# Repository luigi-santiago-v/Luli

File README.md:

# Luli Hydroponics

## Project Overview
This project aims to create a user-friendly, data-driven, and internet-connected hydroponics system. Targeting food deserts, it offers a solution for accessible nutritious food through a smart home appliance. The system integrates temperature/humidity, light intensity, and water pH sensors, along with UV lighting, a water reservoir, a pump, and a microcontroller into a single appliance. It provides real-time plant health and nutrient data, enhanced by a community-driven web application for sharing insights and tips.

## Key Features

- Comprehensive sensor suite for real-time monitoring
- UV lighting and water management for optimal plant growth
- Community web application for knowledge and tips exchange
  - Python Flask + MongoDB backend
- Designed with food deserts and local community reliance in mind
- **Budget:** $500
- **Duration:** 9 months

## Goals
Develop an open-source hydroponic system to enable community-driven, urban agriculture, addressing the challenge of food deserts and their impact on academic performance. The project focuses on simplifying the hydroponics process for beginners, providing a robust system for easy monitoring and maintenance, and fostering community engagement to sustain interest and success in hydroponic gardening.

## Milestones
- Research, design, and component sourcing
- System assembly and testing
- Creation of a functioning prototype from OSB featuring integrated control and monitoring systems
- Demonstration of prototype efficacy with basic crop growth

## Problem Addressed
Tackles the challenges faced by urban growers, including knowledge barriers and the need for continuous system maintenance. Aims to motivate and support users from construction through to the ongoing cultivation process, making hydroponic gardening accessible and engaging.

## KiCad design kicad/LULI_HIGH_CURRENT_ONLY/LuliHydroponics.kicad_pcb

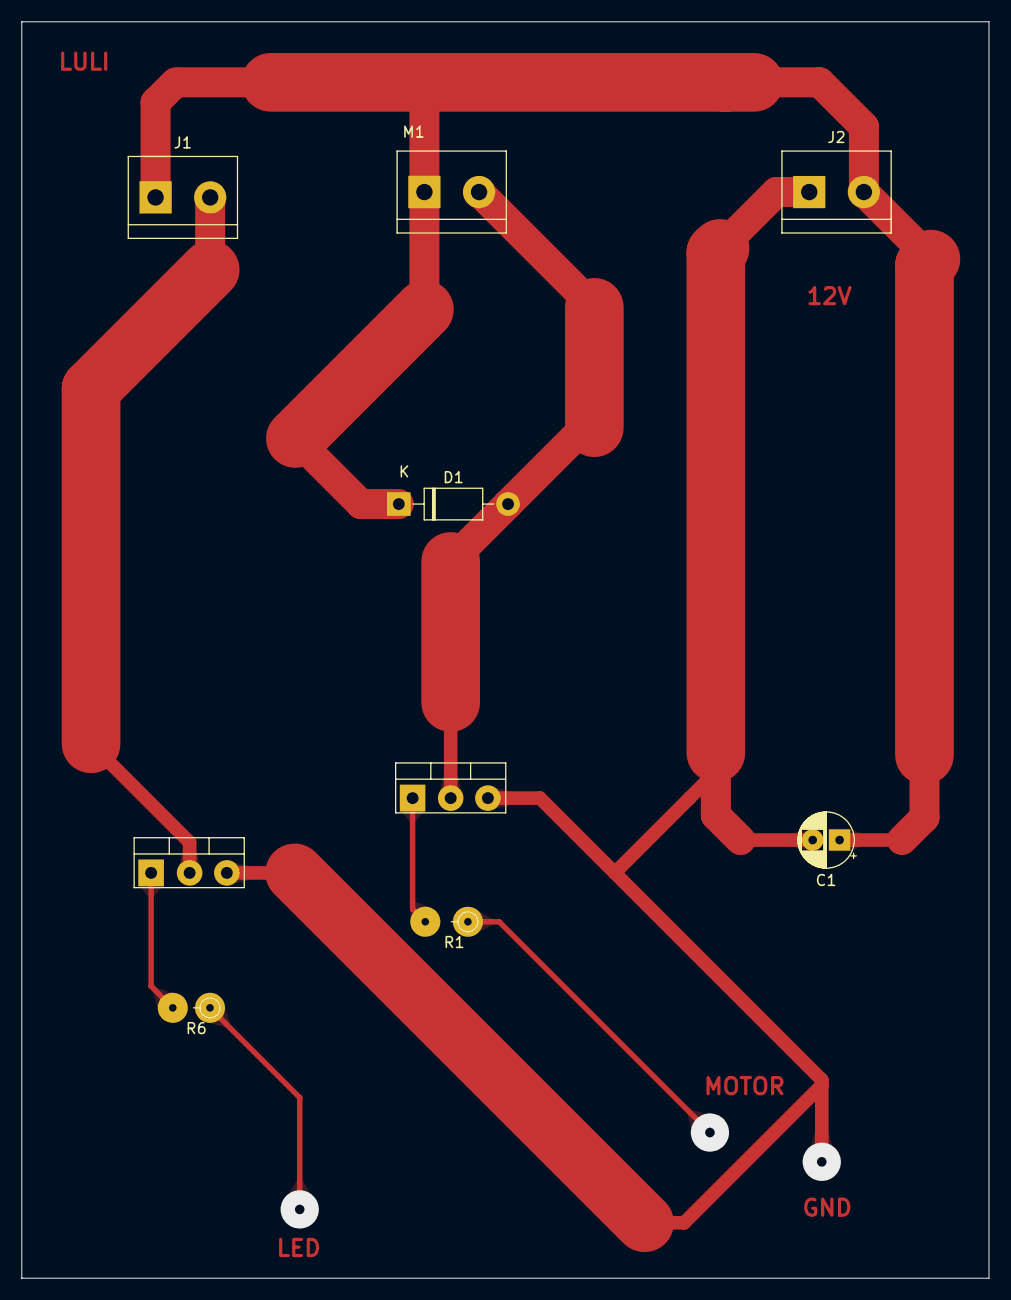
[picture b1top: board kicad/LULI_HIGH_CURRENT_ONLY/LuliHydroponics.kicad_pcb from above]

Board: 2 copper layers, 89.9 x 116.9 mm, 9 parts (0 on the bottom side), 6 nets.

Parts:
C1: 220µF; CP_Radial_D5.0mm_P2.50mm
D1: 1N4001; D_DO-41_SOD81_P10.16mm_Horizontal
J1, J2: Screw_Terminal_01x02; TerminalBlock_bornier-2_P5.08mm
M1: Motor_DC; TerminalBlock_bornier-2_P5.08mm
Q1, Q2: IRLZ34N; TO-220-3_Vertical
R1, R6: 1.0kΩ; R_Axial_DIN0204_L3.6mm_D1.6mm_P2.54mm_Vertical

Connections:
GND: C1.2, J2.1, Q1.3 (S), Q2.3 (S)
unnamed: D1.2 (A), M1.2 (-), Q1.2 (D)
unnamed: J1.2, Q2.2 (D)
unnamed: Q1.1 (G), R1.2
unnamed: Q2.1 (G), R6.2
VCC: C1.1, D1.1 (K), J1.1, J2.2, M1.1 (+)

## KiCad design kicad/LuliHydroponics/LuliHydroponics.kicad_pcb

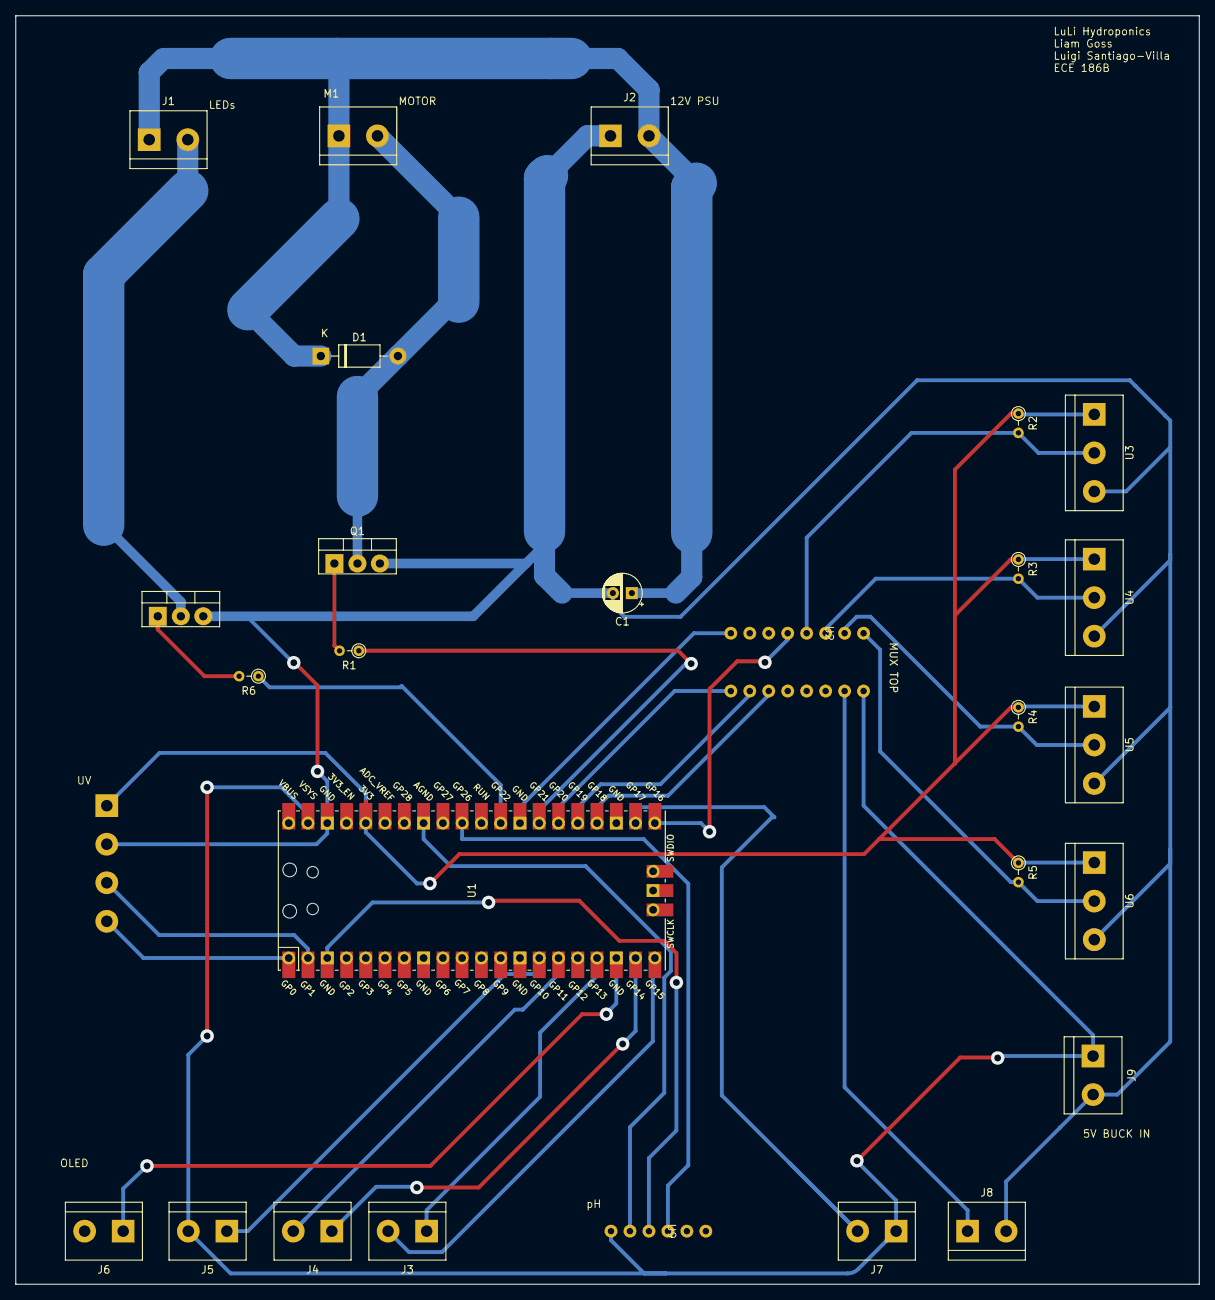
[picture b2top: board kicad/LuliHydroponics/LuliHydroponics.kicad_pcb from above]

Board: 2 copper layers, 156.0 x 167.2 mm, 28 parts (1 on the bottom side), 32 nets.

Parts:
C1: 220µF; CP_Radial_D5.0mm_P2.50mm
D1: 1N4001; D_DO-41_SOD81_P10.16mm_Horizontal
J1, J2, J3, J4, J5, J6, J7, J8, J9: Screw_Terminal_01x02; TerminalBlock_bornier-2_P5.08mm
J10: Screw_Terminal_01x05; TerminalBlock_bornier-4_P5.08mm
M1: Motor_DC; TerminalBlock_bornier-2_P5.08mm
Q1, Q2: IRLZ34N; TO-220-3_Vertical
R1, R6: 1.0kΩ; R_Axial_DIN0204_L3.6mm_D1.6mm_P2.54mm_Vertical
R2, R3, R4, R5: 4.7kΩ; R_Axial_DIN0204_L3.6mm_D1.6mm_P2.54mm_Vertical
U1: Pico; RPi_Pico_SMD_TH
U2: 74LS151
U3, U4, U5, U6: DHT11; TerminalBlock_bornier-3_P5.08mm
U9: PH4502C_Footprint

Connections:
/3V3: J10.1, R2.1, R3.1, R4.1, R5.1, U1.36 (3V3), U3.1 (VDD), U4.1 (VDD), U5.1 (VDD), U6.1 (VDD)
/5V: J5.2, J7.1, J9.1, U1.39 (VSYS), U2.16 (VCC), U9.6 (Vin)
GND: C1.2, J2.1, J8.2, J9.2, J10.2, Q1.3 (S), Q2.3 (S), U1.38 (GND), U3.3 (GND), U4.3 (GND), U5.3 (GND), U6.3 (GND)
unnamed: D1.2 (A), M1.2 (-), Q1.2 (D)
unnamed: J1.2, Q2.2 (D)
unnamed: J3.1, U1.17 (GPIO13)
unnamed: J3.2, U1.20 (GPIO15)
unnamed: J4.1, U1.19 (GPIO14)
unnamed: J4.2, U1.15 (GPIO11)
unnamed: J5.1, U1.14 (GPIO10)
unnamed: J6.1, U1.18 (GND)
unnamed: J7.2, U1.22 (GPIO17)
unnamed: J8.1, U2.15 (I4)
unnamed: J10.3, U1.2 (GPIO1)
unnamed: J10.4, U1.1 (GPIO0)
unnamed: Q1.1 (G), R1.2
unnamed: Q2.1 (G), R6.2
unnamed: U1.33 (AGND), U9.5 (GND)
unnamed: U1.3 (GND), U9.4 (GND)
unnamed: U1.21 (GPIO16), U2.5 (Z)
unnamed: U1.24 (GPIO18), U2.11 (S0)
unnamed: U1.25 (GPIO19), U2.10 (S1)
unnamed: U1.26 (GPIO20), U2.9 (S2)
unnamed: R1.1, U1.27 (GPIO21)
unnamed: R6.1, U1.29 (GPIO22)
unnamed: U1.31 (GPIO26_ADC0), U9.3 (Po)
unnamed: U1.28 (GND), U2.8 (GND)
unnamed: R2.2, U2.4 (I0), U3.2 (DATA)
unnamed: R3.2, U2.3 (I1), U4.2 (DATA)
unnamed: R4.2, U2.2 (I2), U5.2 (DATA)
unnamed: R5.2, U2.1 (I3), U6.2 (DATA)
VCC: C1.1, D1.1 (K), J1.1, J2.2, M1.1 (+)

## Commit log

2024-01-31 Added gitignore and Latex document setup
2024-01-31 Updated Files with Style sheet
2024-02-14 Updated Website apperance
2024-02-14 Updated .gitignore
2024-02-14 Added frontend/backend folder
2024-02-14 Renamed folders, added basic backend PoC
2024-02-14 Added filler text and (incorrect) template to report
2024-02-14 Added login and create account code
2024-02-14 Added requirements.txt
2024-02-14 Changes to Login.html and main.py
2024-02-16 added multiple login routes
2024-02-21 Updated the website layout
2024-02-21 Updated login code, added session, renamed routes
2024-02-21 Added logout func
2024-02-26 Updated abstract and overview of report
2024-03-02 updated abstract
2024-03-06 Added Pico code folder
2024-03-06 Added UV pico code
2024-03-11 Added SSL on server, reflected port change in app startup
2024-03-13 Added to backend/server part of report
2024-03-20 Push before merge
2024-03-20 updated Files
2024-03-20 rm sync file
2024-03-20 Converted indents
2024-03-20 Added boilerplate api functions
2024-03-20 Updated api function structure, removed circular imports
2024-04-10 Added basic messaging and following system tests
2024-04-10 Renamed function parameters for clarity
2024-04-10 Dropped friends collection, moved to credentials, made it a followers list
2024-04-10 Added function to get most recent message from specific user
2024-04-11 pH sensor code added
2024-04-12 new url commit
2024-04-12 Added report images to git ignore
2024-04-12 Added Pico LED control mosfet code
2024-04-12 Added .gz to gitignore
2024-04-12 Updated Liam individual report
2024-04-13 updated my branch
2024-04-14 Added motor control code
2024-04-15 Added motor and led combined test pico code
2024-04-15 updating files
2024-04-15 Added sensor test data
2024-04-15 Added jinja support to plants.html
2024-04-24 Combined Pico code
2024-04-24 Added source url comment to Luli_UV.py
2024-04-26 Updated Pico Code
2024-04-26 Updated API key validation
2024-04-26 Pico main code changes, config changes
2024-04-26 Pico code working as expected, debugging changes
2024-04-27 update front end for final testing
2024-04-27 Moved images and scripts in frontend
2024-04-27 Added forum image support
2024-04-28 Added control panel
2024-04-29 Liam Individual report complete
2024-04-30 Group report created and finished
2024-05-02 Final commit
2024-05-02 Added schematic and PCB files
